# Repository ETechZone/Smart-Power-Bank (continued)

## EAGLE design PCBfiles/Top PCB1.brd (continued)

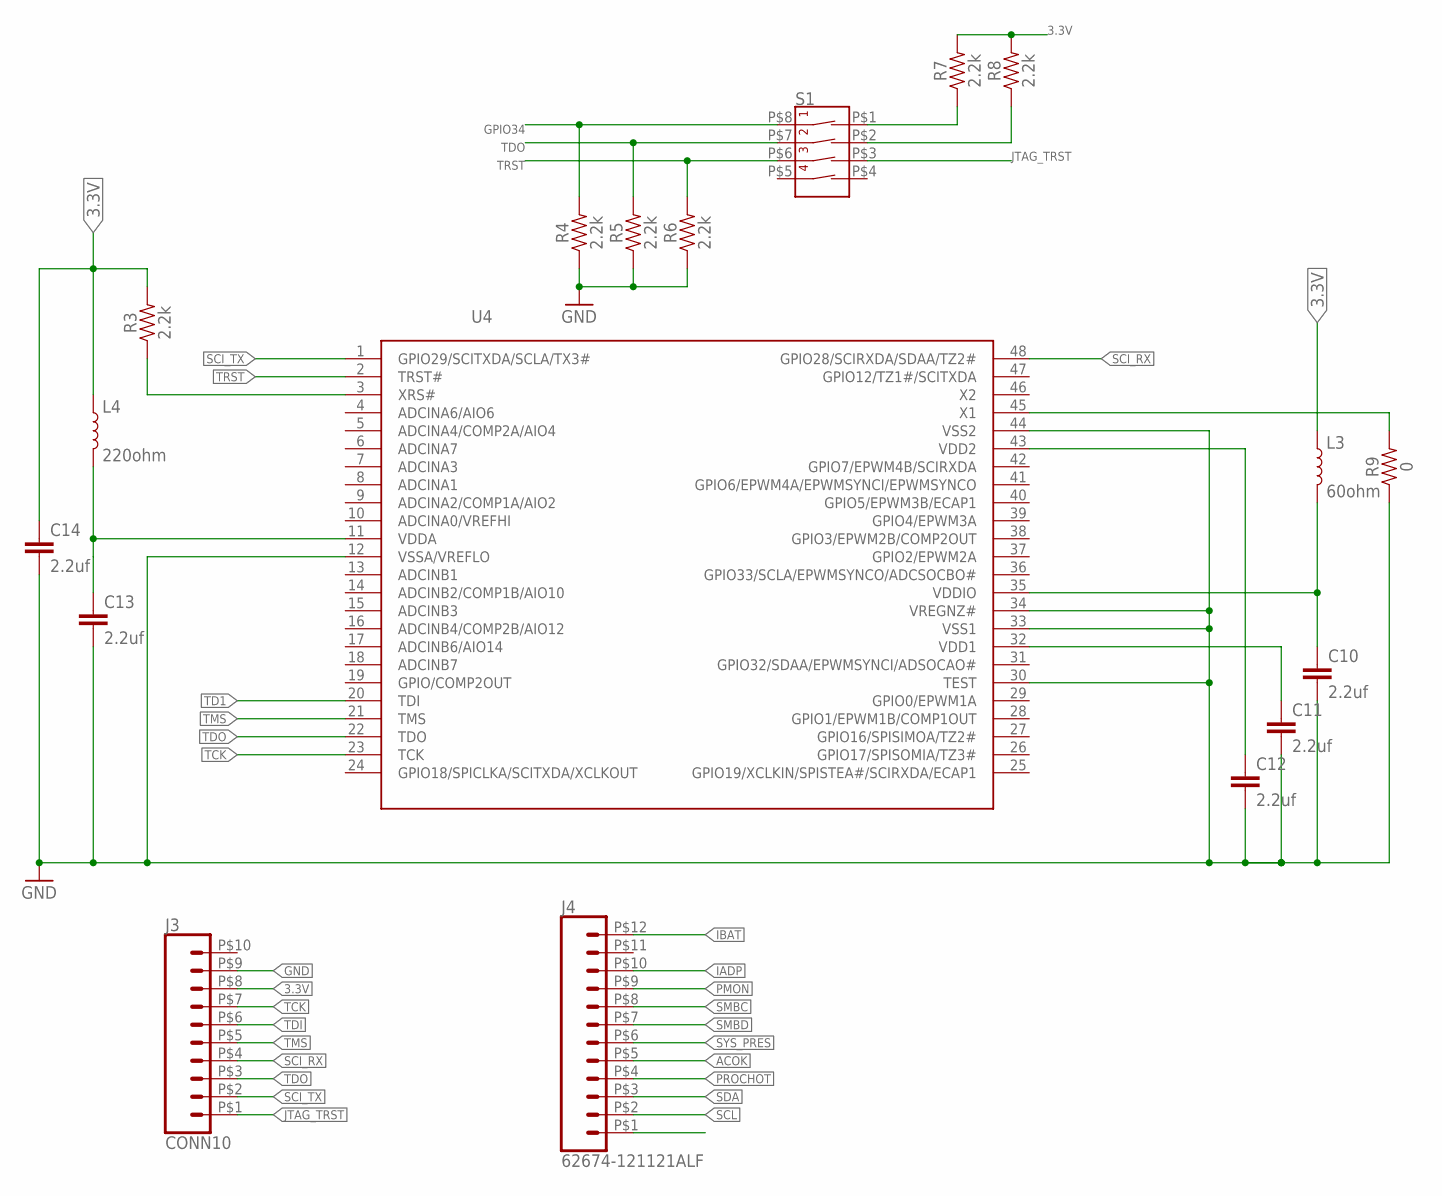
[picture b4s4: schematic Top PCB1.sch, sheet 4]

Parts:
C10, C11, C12, C13, C14: 2.2uf; C0402K
J3: CONN10; CONN10_1.27
J4: 62674-121121ALF
L3: 60ohm; BEADC1005X50
L4: 220ohm; BEADC1005X50
R3, R4, R5, R6, R7, R8: 2.2k; 0402
R9: 0; 0402
S1: DHN-04-V
U4: TMS320F28027; QFP50P900X900X145-48

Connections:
3.3V: C14.1, J3.P$8 (8), L3.1, L4.1, R3.2, R7.2, R8.2; also elsewhere on the board
ACOK: J4.P$5 (5)
GND: C10.2, C11.2, C12.2, C13.2, C14.2, J3.P$9 (9), R4.1, R5.1, R6.1, R9.1, U4.12 (VSSA/VREFLO), U4.30 (TEST), U4.33 (VSS1), U4.34 (VREGNZ#), U4.44 (VSS2)
GPIO34: R4.2, S1.P$8 (1B)
IADP: J4.P$10 (10)
IBAT: J4.P$12 (12)
JTAG_TRST: J3.P$1 (1), S1.P$3 (3A)
unnamed: R9.2, U4.45 (X1)
unnamed: C10.1, L3.2, U4.35 (VDDIO)
unnamed: C11.1, U4.32 (VDD1)
unnamed: C12.1, U4.43 (VDD2)
unnamed: C13.1, L4.2, U4.11 (VDDA)
unnamed: R3.1, U4.3 (XRS#)
unnamed: R7.1, S1.P$1 (1A)
unnamed: R8.1, S1.P$2 (2A)
PMON: J4.P$9 (9)
PROCHOT: J4.P$4 (4)
SCI_RX: J3.P$4 (4), U4.48 (GPIO28/SCIRXDA/SDAA/TZ2#)
SCI_TX: J3.P$2 (2), U4.1 (GPIO29/SCITXDA/SCLA/TX3#)
SCL: J4.P$2 (2)
SDA: J4.P$3 (3)
SMBC: J4.P$8 (8)
SMBD: J4.P$7 (7)
SYS_PRES: J4.P$6 (6)
TCK: J3.P$7 (7), U4.23 (TCK)
TD1: U4.20 (TDI)
TDI: J3.P$6 (6)
TDO: J3.P$3 (3), R5.2, S1.P$7 (2B), U4.22 (TDO)
TMS: J3.P$5 (5), U4.21 (TMS)
TRST: R6.2, S1.P$6 (3B), U4.2 (TRST#)

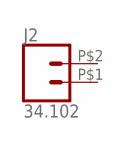
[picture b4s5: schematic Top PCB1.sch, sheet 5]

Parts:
J2: 34.102

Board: 2 copper layers, 50 parts (0 on the bottom side), 39 nets, no tracks yet.

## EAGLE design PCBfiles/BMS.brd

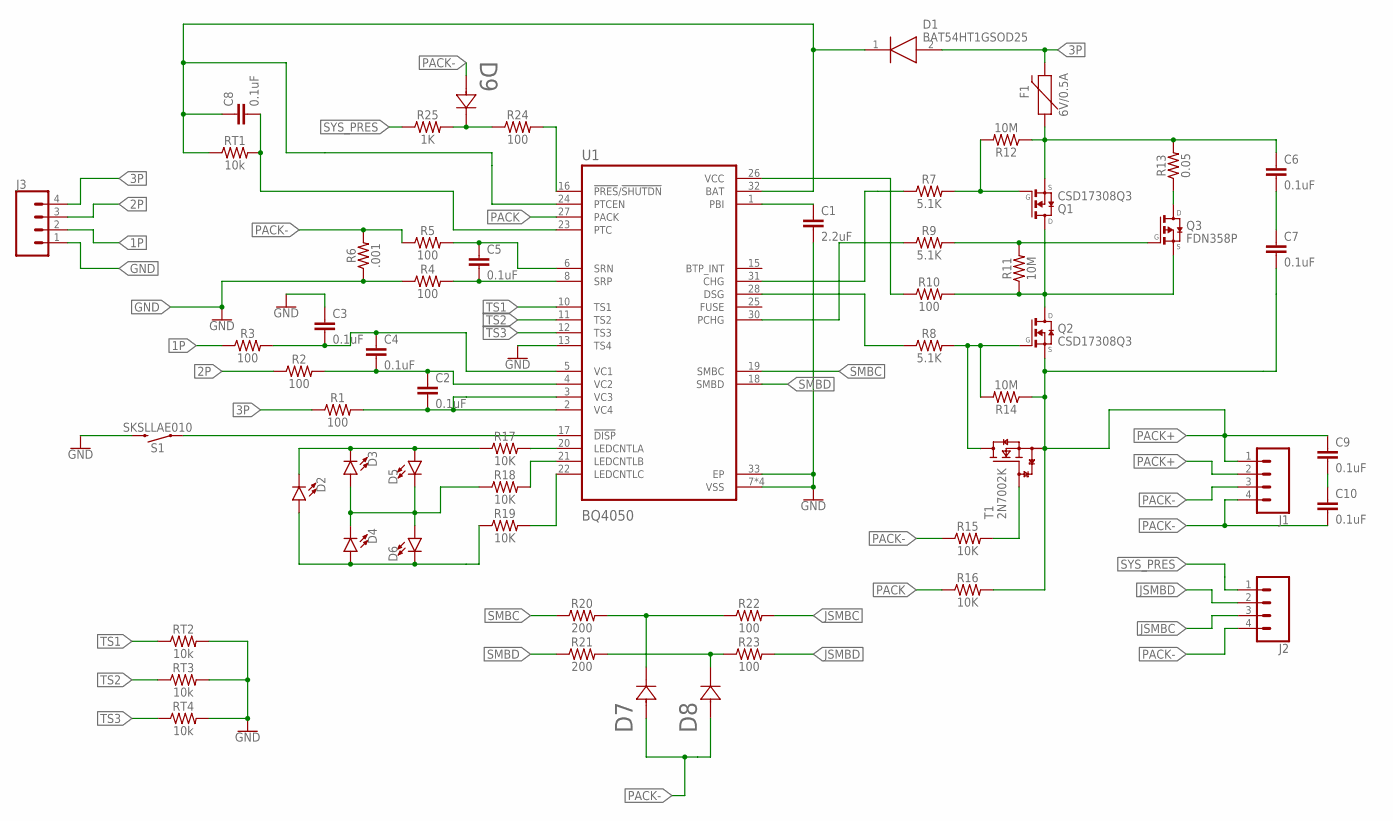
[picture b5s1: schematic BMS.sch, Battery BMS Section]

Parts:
C1: 2.2uF; 0402-CAP
C2, C3, C4, C5, C6, C7, C8, C9, C10: 0.1uF; 0402
D1: BAT54HT1GSOD25; SOD2512X100
D2, D3, D4, D5, D6: LTW-S272TLA-1175391
D7: D7; SODFL2513X100
D8: D8; SODFL2513X100
D9: D9; SODFL2513X100
F1: 6V/0.5A; 1206
J1, J2: CONN_041.3HOLE; 1X04_1.3HOLE
J3: CONN_041X04_NO_SILK; 1X04_NO_SILK
Q1, Q2: CSD17308Q3; SON8-Q3
Q3: FDN358P; SSOT-3
R1, R2, R3, R4, R5, R10, R22, R23, R24: 100; 0402
R6: .001; RESC3015X65
R7, R8, R9: 5.1K; 0402
R11, R12, R14: 10M; 0402
R13: 0.05; 2512
R15, R16, R17, R18, R19: 10K; 0402
R20, R21: 200; 0402
R25: 1K; 0402
RT1: 10k; 1206
RT2, RT3, RT4: 10k; NTC-RESISTOR
S1: SKSLLAE010; SWITCH
T1: 2N7002K; SOT23
U1: BQ4050; QFN40P400X400X100-33T140

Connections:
1P: J3.2, R3.1
2P: J3.3, R2.1
3P: D1.2 (A), F1.2, J3.4, R1.1
GND: C1.2, C3.1, J3.1, R4.1, R6.1, RT2.2, RT3.2, RT4.2, S1.P$2 (2), U1.7 (VSS), U1.9 (VSS), U1.13 (TS4), U1.14 (VSS), U1.29 (VSS), U1.33 (EP)
JSMBC: J2.3, R22.2
JSMBD: J2.2, R23.2
unnamed: C1.1, U1.1 (PBI)
unnamed: C5.2, R4.2, U1.8 (SRP)
unnamed: S1.P$1 (1), U1.17 (!DISP)
unnamed: C3.2, C4.1, R3.2, U1.5 (VC1)
unnamed: C2.2, R1.2, U1.2 (VC4), U1.3 (VC3)
unnamed: C5.1, R5.2, U1.6 (SRN)
unnamed: C2.1, C4.2, R2.2, U1.4 (VC2)
unnamed: Q1.4 (G), R7.2, R12.2
unnamed: R7.1, U1.31 (CHG)
unnamed: R8.1, U1.28 (DSG)
unnamed: Q2.4 (G), R8.2, R14.2, T1.3 (D)
unnamed: Q1.5 (D), Q1.6 (D), Q1.7 (D), Q1.8 (D), Q2.5 (D), Q2.6 (D), Q2.7 (D), Q2.8 (D), Q3.2 (S), R10.2, R11.1
unnamed: R10.1, U1.26 (VCC)
unnamed: R9.1, U1.30 (PCHG)
unnamed: Q3.1 (G), R9.2, R11.2
unnamed: Q3.3 (D), R13.P$1 (1)
unnamed: R15.2, T1.1 (G)
unnamed: C6.2, C7.1
unnamed: R17.2, U1.20 (LEDCNTLA)
unnamed: D2.P$1 (C), D3.P$1 (C), D5.P$2 (A), R17.1
unnamed: D2.P$2 (A), D4.P$2 (A), D6.P$1 (C), R19.1
unnamed: R19.2, U1.22 (LEDCNTLC)
unnamed: R18.2, U1.21 (LEDCNTLB)
unnamed: D3.P$2 (A), D4.P$1 (C), D5.P$1 (C), D6.P$2 (A), R18.1
unnamed: D7.1, R20.2, R22.1
unnamed: D8.1, R21.2, R23.1
unnamed: C9.2, C10.1
unnamed: C6.1, F1.1, Q1.1 (S), Q1.2 (S), Q1.3 (S), R12.1, R13.P$2 (2)
unnamed: R24.2, U1.16 (!PRES!/!SHUTDN)
unnamed: D9.1, R24.1, R25.2
unnamed: C8.2, RT1.2, U1.23 (PTC)
unnamed: C8.1, D1.1 (K), RT1.1, U1.24 (PTCEN), U1.32 (BAT)
PACK: R16.1, U1.27 (PACK)
PACK+: C7.2, C9.1, J1.1, J1.2, Q2.1 (S), Q2.2 (S), Q2.3 (S), R14.1, R16.2, T1.2 (S)
PACK-: C10.2, D7.2, D8.2, D9.2, J1.3, J1.4, J2.4, R5.1, R6.2, R15.1
SMBC: R20.1, U1.19 (SMBC)
SMBD: R21.1, U1.18 (SMBD)
SYS_PRES: J2.1, R25.1
TS1: RT2.1, U1.10 (TS1)
TS2: RT3.1, U1.11 (TS2)
TS3: RT4.1, U1.12 (TS3)

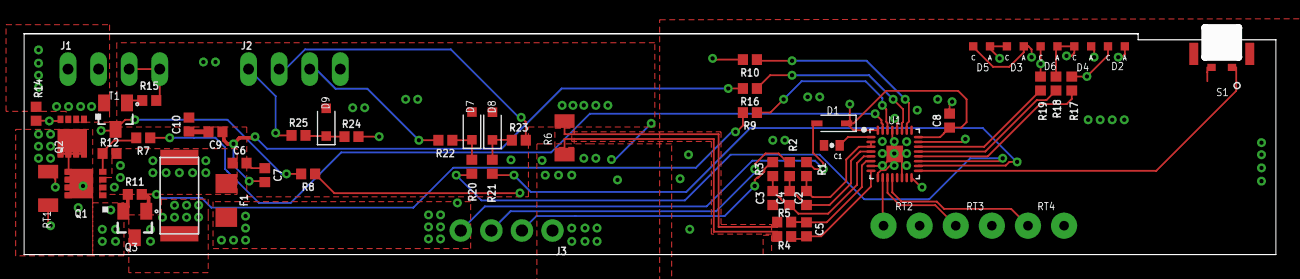
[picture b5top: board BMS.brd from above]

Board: 4 copper layers, 103.4 x 18.6 mm, 58 parts (0 on the bottom side), 47 nets.

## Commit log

2019-07-15 sample commit
2019-07-16 main program
2019-07-16 branch file and their hederfiles
2019-07-16 contents of headers
2019-07-16 setting contents
2019-07-17 pcbfiles
2019-07-17 supporting doccuments
2019-07-17 PCB files
2019-07-17 programming
2019-07-17 c file deletion
2019-07-17 supporting docccuments
2019-07-17 supporitng docs update
2019-07-18 adding new delop branch
2019-07-18 feature commit
2019-07-18 develop1
2019-07-18 commit by second user
2019-07-18 user2 commit
